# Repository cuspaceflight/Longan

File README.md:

# Longan
 Minimal Avionics for High Altitude Ballooning

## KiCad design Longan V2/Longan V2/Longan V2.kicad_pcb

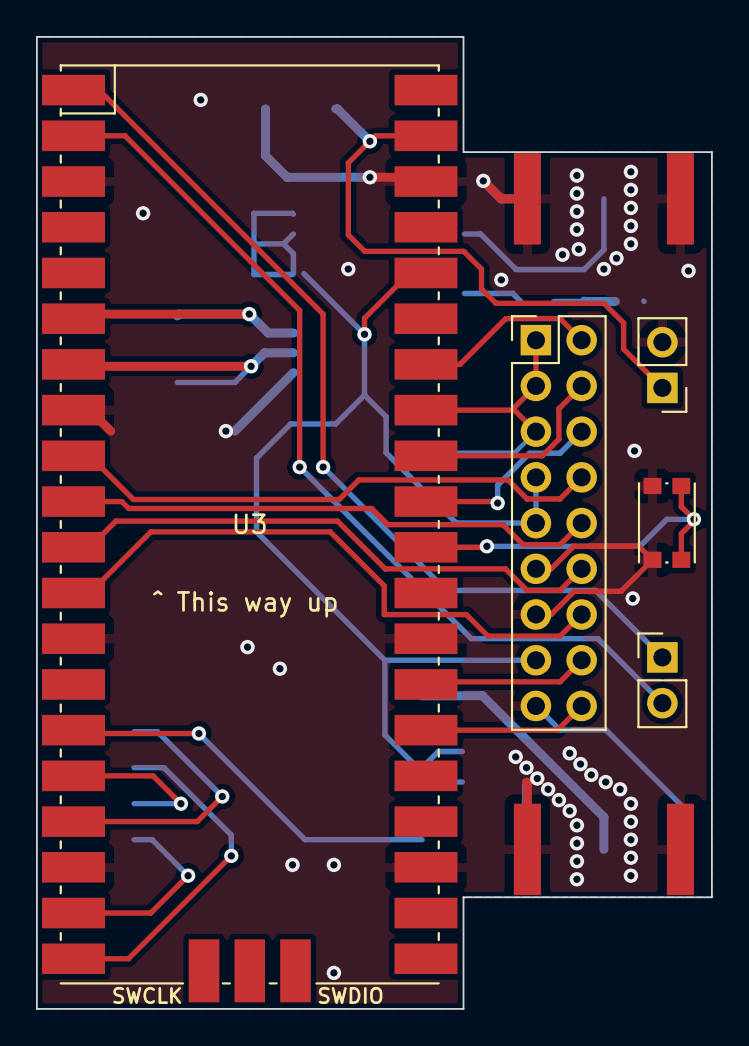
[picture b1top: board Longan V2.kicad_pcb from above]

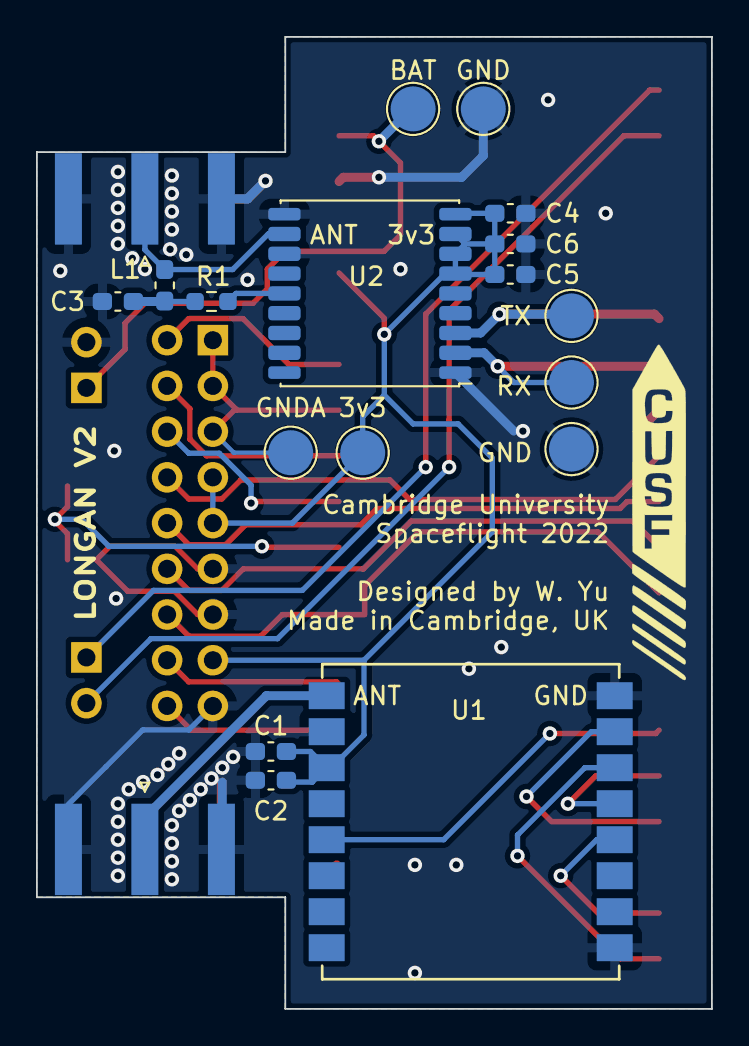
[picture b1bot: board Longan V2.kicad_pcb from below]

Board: 2 copper layers, 37.5 x 54.0 mm, 24 parts (19 on the bottom side), 27 nets.

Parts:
3v3: 3v3; TestPoint_Pad_D2.5mm
BAT: Bat; TestPoint_Pad_D2.5mm
C1: 22u; C_0603_1608Metric_Pad1.08x0.95mm_HandSolder
C2, C4: 0.1u; C_0603_1608Metric_Pad1.08x0.95mm_HandSolder
C3: 10n; C_0603_1608Metric_Pad1.08x0.95mm_HandSolder
C5: 1u; C_0603_1608Metric_Pad1.08x0.95mm_HandSolder
C6: 0.1n; C_0603_1608Metric_Pad1.08x0.95mm_HandSolder
GND: GND; TestPoint_Pad_D2.5mm
GND#2: GND; TestPoint_Pad_D2.5mm
GNDA: GNDA; TestPoint_Pad_D2.5mm
J1, J2: Conn_Coaxial; SMA_Amphenol_132289_EdgeMount
J3: Conn_02x09_Odd_Even; PinHeader_2x09_P2.54mm_Vertical
J5: Battery; PinHeader_1x02_P2.54mm_Vertical
J6: Serial Output; PinHeader_1x02_P2.54mm_Vertical
L1: 27n; L_0603_1608Metric_Pad1.05x0.95mm_HandSolder
R1: 10; R_0603_1608Metric_Pad0.98x0.95mm_HandSolder
RX: GPS_RX; TestPoint_Pad_D2.5mm
SW1: Reset SW; SW_Push_1P1T_NO_CK_KMR2
TX: GPS_TX; TestPoint_Pad_D2.5mm
U1: Ai-Thinker-Ra-01; Ai-Thinker-Ra-01-LoRa
U2: MAX-M8Q; ublox_MAX
U3: Pico; RPi_Pico_SMD

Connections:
+3V3: 3v3.1, C1.2, C2.2, C4.2, C5.2, C6.2, J3.7, J3.9, J3.15, U1.3 (VDD), U2.6 (V_BCKP), U2.7 (VCC_IO), U2.8 (VCC), U2.9 (~RESET), U3.36 (3V3)
/ADC_0: J3.6, U3.31 (GPIO26_ADC0)
/ADC_1: J3.4, U3.32 (GPIO27_ADC1)
/ADC_2: J3.2, U3.34 (GPIO28_ADC2)
/BAT_IN: BAT.1, J5.1, U3.39 (VSYS)
/CS_LOR: U1.15 (~NSS), U3.17 (GPIO13)
/DIO_0: U1.5 (DIO0), U3.15 (GPIO11)
/GPIO_1: J3.8, U3.9 (GPIO6)
/GPIO_2: J3.10, U3.10 (GPIO7)
/GPIO_3: J3.12, U3.11 (GPIO8)
/GPIO_4: J3.14, U3.12 (GPIO9)
/MISO_1: U1.13 (MISO), U3.16 (GPIO12)
/MOSI_1: U1.14 (MOSI), U3.20 (GPIO15)
/RX_0: J6.2, U3.2 (GPIO1)
/RX_1: RX.1, U2.2 (TXD), U3.7 (GPIO5)
/SCLK_1: U1.12 (SCK), U3.19 (GPIO14)
/SCL_0: J3.16, U3.27 (GPIO21)
/SDA_0: J3.18, U3.26 (GPIO20)
/TX_0: J6.1, U3.1 (GPIO0)
/TX_1: TX.1, U2.3 (RXD), U3.6 (GPIO4)
GND: C1.1, C2.1, C3.1, C4.1, C5.1, C6.1, GND.1, GND#2.1, J1.2 (Ext), J2.2 (Ext), J3.11, J3.13, J3.17, J5.2, SW1.2, U1.2 (GND), U1.9 (GND), U1.16 (GND), U2.1 (GND), U2.10 (GND), U2.12 (GND), U3.3 (GND), U3.8 (GND), U3.13 (GND), U3.18 (GND), U3.23 (GND), U3.28 (GND), U3.38 (GND)
GNDA: GNDA.1, J3.1, J3.3, J3.5, U3.33 (AGND)
unnamed: C3.2, L1.1, R1.2
unnamed: J1.1 (In), U1.1 (ANT)
unnamed: J2.1 (In), L1.2, U2.11 (RF_IN)
unnamed: R1.1, U2.14 (VCC_RF)
unnamed: SW1.1, U3.30 (RUN)

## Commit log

2022-11-22 Polishing
    - More vias
    - Test points
    - Narrower zones
    - Logo
    - Pin Labels
